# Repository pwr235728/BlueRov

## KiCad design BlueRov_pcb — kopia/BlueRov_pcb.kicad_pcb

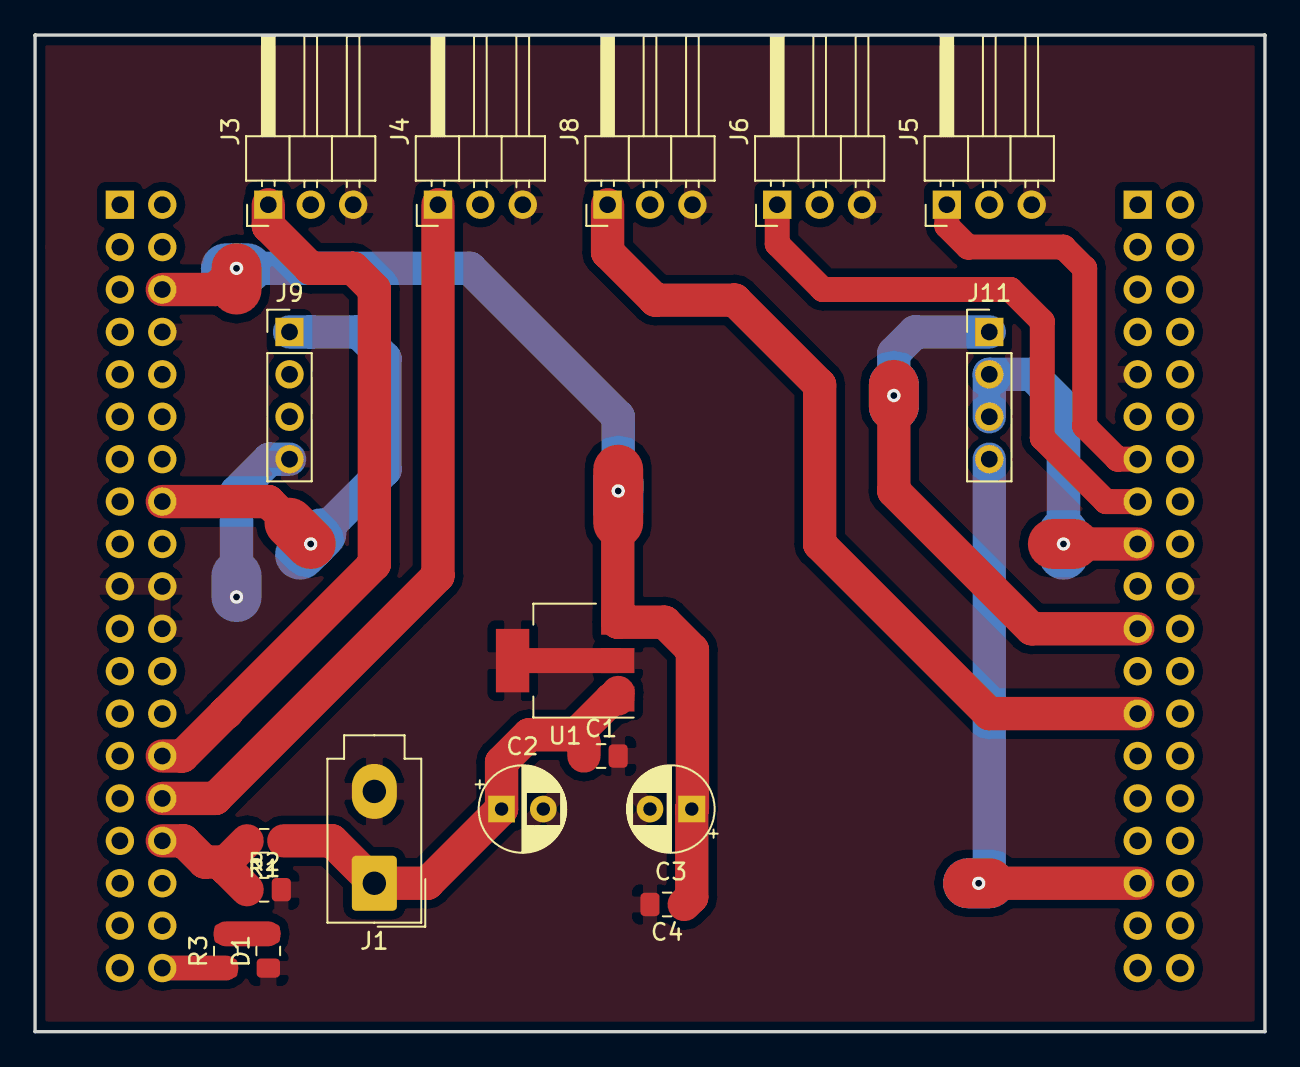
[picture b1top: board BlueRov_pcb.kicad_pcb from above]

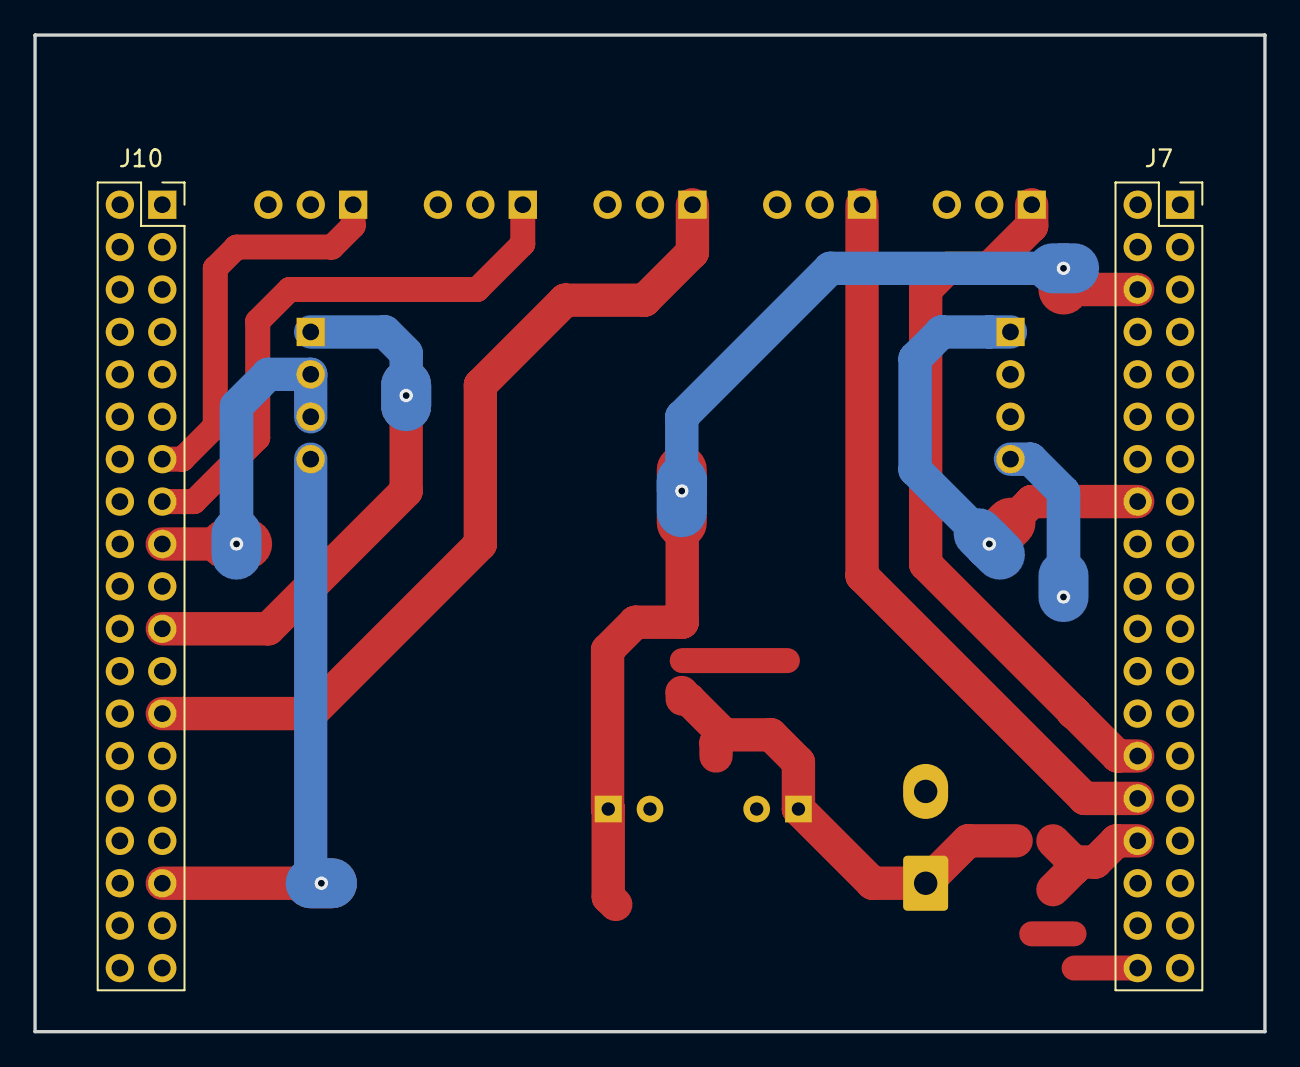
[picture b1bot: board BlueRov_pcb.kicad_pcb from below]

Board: 2 copper layers, 73.7 x 59.7 mm, 19 parts (2 on the bottom side), 15 nets.

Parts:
C1, C4: 100n; C_0805_2012Metric_Pad1.15x1.40mm_HandSolder
C2, C3: 22u; CP_Radial_D5.0mm_P2.50mm
D1: LED; C_0805_2012Metric_Pad1.15x1.40mm_HandSolder
J1: Vin; Molex_Mini-Fit_Jr_5566-02A_2x01_P4.20mm_Vertical
J3, J4, J5, J6, J8: Conn_01x03; PinHeader_1x03_P2.54mm_Horizontal
J7, J10: Conn_02x19_Odd_Even; PinSocket_2x19_P2.54mm_Vertical
J9, J11: Conn_01x04; PinHeader_1x04_P2.54mm_Vertical
R1: 15k; R_0805_2012Metric_Pad1.15x1.40mm_HandSolder
R2: 3k; R_0805_2012Metric_Pad1.15x1.40mm_HandSolder
R3: 470; R_0805_2012Metric_Pad1.15x1.40mm_HandSolder
U1: L7805; SOT-223-3_TabPin2

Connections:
+3V3: J7.16, J9.1
+5V: C3.1, C4.1, J7.6, U1.3
ADC: J7.32, R1.2, R2.1
DE: J10.17, J11.2, J11.3
DI: J10.21, J11.1
GND: C1.2, C2.2, C3.2, C4.2, D1.1, J1.2, J3.3, J4.3, J5.3, J6.3, J7.8, J7.19, J7.20, J7.22, J8.3, J9.4, J10.9, J10.20, R2.2, U1.2
unnamed: D1.2, R3.2
RO: J10.33, J11.4
TIM2_CH1: J3.1, J7.28
TIM2_CH2: J4.1, J7.30
TIM3_CH1: J5.1, J10.13
TIM3_CH2: J6.1, J10.15
TIM3_CH3: J8.1, J10.25
USER_LED: J7.38, R3.1
VCC: C1.1, C2.1, J1.1, R1.1, U1.1

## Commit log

2019-08-15 Existing files
2019-08-29 szyk pcb
